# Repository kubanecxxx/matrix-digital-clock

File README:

matrix-digital-clock
====================

Digital clock with homemade LED matrix; STM32 microcontroler; ChibiOS real time operating system

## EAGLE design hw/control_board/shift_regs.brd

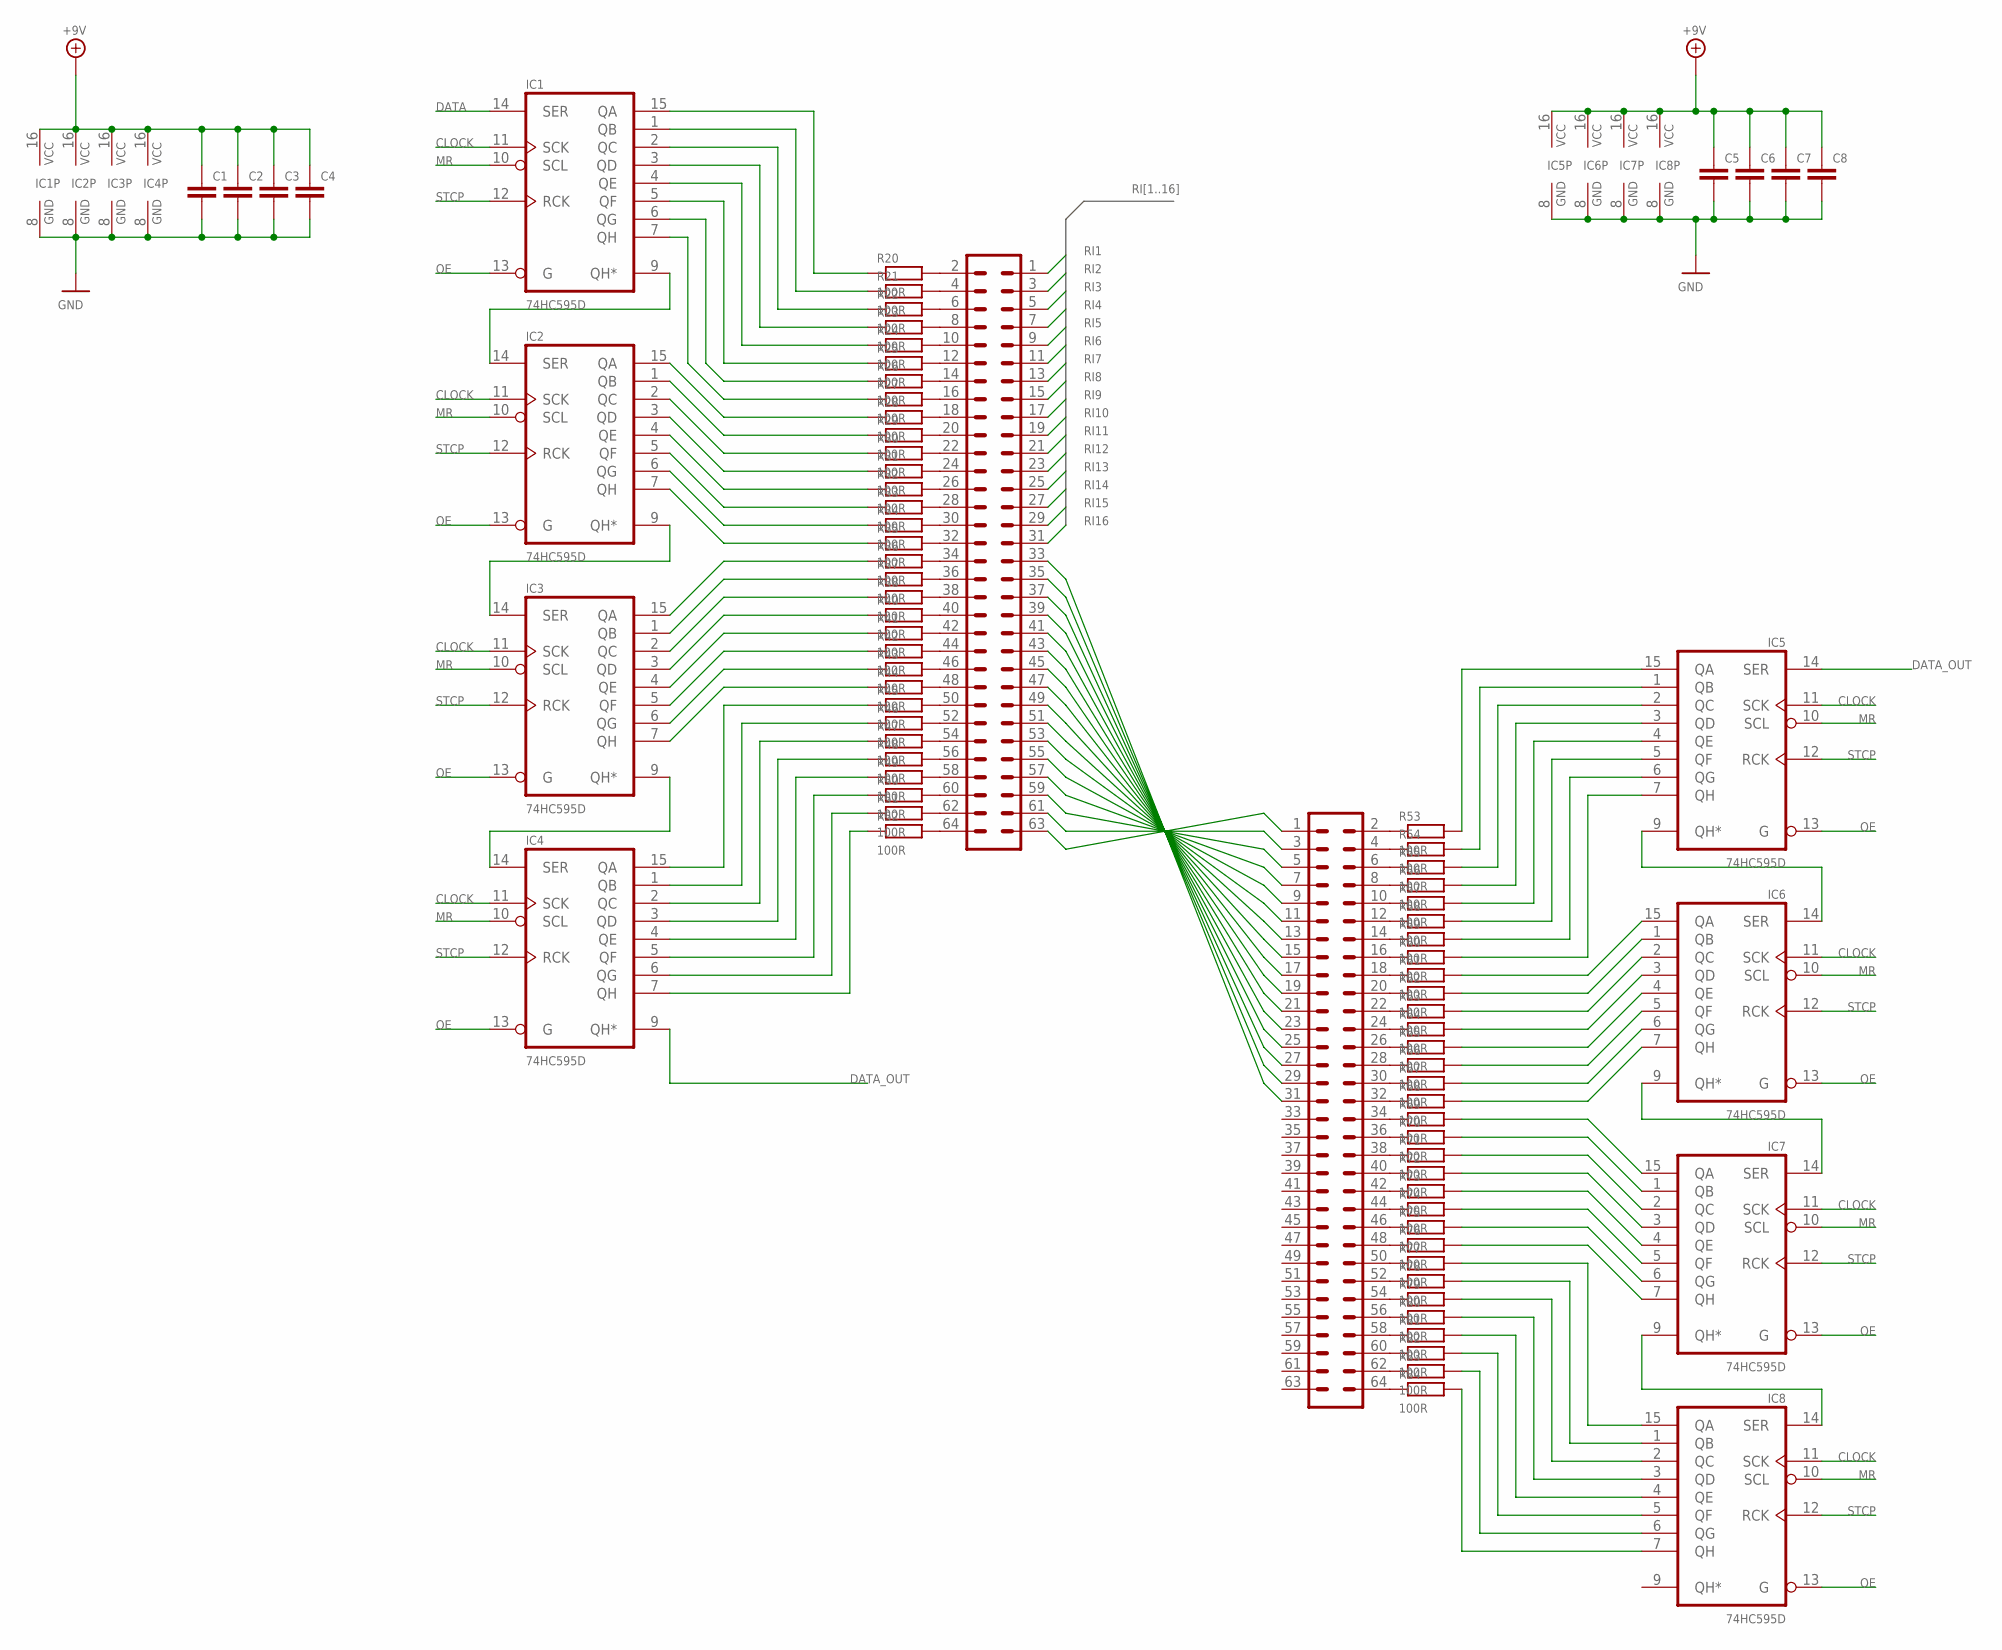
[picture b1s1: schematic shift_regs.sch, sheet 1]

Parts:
C1, C2, C3, C4, C5, C6, C7, C8: C-EUC0805; C0805
IC1, IC2, IC3, IC4, IC5, IC6, IC7, IC8: 74HC595D; SO16
R20, R21, R22, R23, R24, R25, R26, R27, R28, R29, R30, R31, R32, R33, R34, R35, R36, R37, R38, R40, R41, R42, R43, R44, R45, R46, R47, R48, R49, R50, R51, R52, R53, R54, R55, R56, R57, R58, R59, R60, R61, R62, R63, R64, R65, R66, R67, R68, R69, R70, R71, R72, R73, R74, R75, R76, R77, R78, R79, R80, R81, R82, R83, R84: 100R; R0805
SV1, SV2: ML64

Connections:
+9V: C1.1, C2.1, C3.1, C4.1, C5.1, C6.1, C7.1, C8.1, IC1.16 (VCC), IC2.16 (VCC), IC3.16 (VCC), IC4.16 (VCC), IC5.16 (VCC), IC6.16 (VCC), IC7.16 (VCC), IC8.16 (VCC); also elsewhere on the board
CLOCK: IC1.11 (SCK), IC2.11 (SCK), IC3.11 (SCK), IC4.11 (SCK), IC5.11 (SCK), IC6.11 (SCK), IC7.11 (SCK), IC8.11 (SCK); also elsewhere on the board
DATA: IC1.14 (SER); also elsewhere on the board
DATA_OUT: IC4.9 (QH*), IC5.14 (SER)
GND: C1.2, C2.2, C3.2, C4.2, C5.2, C6.2, C7.2, C8.2, IC1.8 (GND), IC2.8 (GND), IC3.8 (GND), IC4.8 (GND), IC5.8 (GND), IC6.8 (GND), IC7.8 (GND), IC8.8 (GND); also elsewhere on the board
MR: IC1.10 (SCL), IC2.10 (SCL), IC3.10 (SCL), IC4.10 (SCL), IC5.10 (SCL), IC6.10 (SCL), IC7.10 (SCL), IC8.10 (SCL); also elsewhere on the board
unnamed: IC1.9 (QH*), IC2.14 (SER)
unnamed: IC2.9 (QH*), IC3.14 (SER)
unnamed: IC3.9 (QH*), IC4.14 (SER)
unnamed: IC1.1 (QB), R21.1
unnamed: IC1.2 (QC), R22.1
unnamed: IC1.3 (QD), R23.1
unnamed: IC1.4 (QE), R24.1
unnamed: IC1.5 (QF), R25.1
unnamed: IC1.6 (QG), R26.1
unnamed: IC1.7 (QH), R27.1
unnamed: IC1.15 (QA), R20.1
unnamed: IC2.1 (QB), R29.1
unnamed: IC2.2 (QC), R30.1
unnamed: IC2.3 (QD), R31.1
unnamed: IC2.4 (QE), R32.1
unnamed: IC2.5 (QF), R33.1
unnamed: IC2.6 (QG), R34.1
unnamed: IC2.7 (QH), R35.1
unnamed: IC2.15 (QA), R28.1
unnamed: IC3.1 (QB), R37.1
unnamed: IC3.2 (QC), R38.1
unnamed: IC3.3 (QD), R40.1
unnamed: IC3.4 (QE), R41.1
unnamed: IC3.5 (QF), R42.1
unnamed: IC3.6 (QG), R43.1
unnamed: IC3.7 (QH), R44.1
unnamed: IC3.15 (QA), R36.1
unnamed: R20.2, SV1.2
unnamed: R21.2, SV1.4
unnamed: R22.2, SV1.6
unnamed: R23.2, SV1.8
unnamed: R24.2, SV1.10
unnamed: R25.2, SV1.12
unnamed: R26.2, SV1.14
unnamed: R27.2, SV1.16
unnamed: IC5.9 (QH*), IC6.14 (SER)
unnamed: IC6.9 (QH*), IC7.14 (SER)
unnamed: IC7.9 (QH*), IC8.14 (SER)
unnamed: IC5.1 (QB), R54.2
unnamed: IC5.2 (QC), R55.2
unnamed: IC5.3 (QD), R56.2
unnamed: IC5.4 (QE), R57.2
unnamed: IC5.5 (QF), R58.2
unnamed: IC5.6 (QG), R59.2
unnamed: IC5.7 (QH), R60.2
unnamed: IC5.15 (QA), R53.2
unnamed: IC6.1 (QB), R62.2
unnamed: IC6.2 (QC), R63.2
unnamed: IC6.3 (QD), R64.2
unnamed: IC6.4 (QE), R65.2
unnamed: IC6.5 (QF), R66.2
unnamed: IC6.6 (QG), R67.2
unnamed: IC6.7 (QH), R68.2
unnamed: IC6.15 (QA), R61.2
unnamed: IC7.1 (QB), R70.2
unnamed: IC7.2 (QC), R71.2
unnamed: IC7.3 (QD), R72.2
unnamed: IC7.4 (QE), R73.2
unnamed: IC7.5 (QF), R74.2
unnamed: IC7.6 (QG), R75.2
unnamed: IC7.7 (QH), R76.2
unnamed: IC7.15 (QA), R69.2
unnamed: IC8.15 (QA), R77.2
unnamed: IC8.1 (QB), R78.2
unnamed: IC8.2 (QC), R79.2
unnamed: IC8.3 (QD), R80.2
unnamed: IC8.4 (QE), R81.2
unnamed: IC8.5 (QF), R82.2
unnamed: IC8.6 (QG), R83.2
unnamed: IC8.7 (QH), R84.2
unnamed: SV1.63, SV2.1
unnamed: SV1.61, SV2.3
unnamed: SV1.59, SV2.5
unnamed: SV1.57, SV2.7
unnamed: SV1.55, SV2.9
unnamed: SV1.53, SV2.11
unnamed: SV1.51, SV2.13
unnamed: SV1.49, SV2.15
unnamed: SV1.47, SV2.17
unnamed: SV1.45, SV2.19
unnamed: SV1.43, SV2.21
unnamed: SV1.41, SV2.23
unnamed: SV1.39, SV2.25
unnamed: SV1.37, SV2.27
unnamed: SV1.35, SV2.29
unnamed: SV1.33, SV2.31
unnamed: R28.2, SV1.18
unnamed: R29.2, SV1.20
unnamed: R30.2, SV1.22
unnamed: R31.2, SV1.24
unnamed: R32.2, SV1.26
unnamed: R33.2, SV1.28
unnamed: R34.2, SV1.30
unnamed: R35.2, SV1.32
unnamed: R36.2, SV1.34
unnamed: R37.2, SV1.36
unnamed: R38.2, SV1.38
unnamed: R40.2, SV1.40
unnamed: R41.2, SV1.42
unnamed: R42.2, SV1.44
unnamed: R43.2, SV1.46
unnamed: R44.2, SV1.48
unnamed: R45.2, SV1.50
unnamed: R46.2, SV1.52
unnamed: R47.2, SV1.54
unnamed: R48.2, SV1.56
unnamed: R49.2, SV1.58
unnamed: R50.2, SV1.60
unnamed: R51.2, SV1.62
unnamed: R52.2, SV1.64
unnamed: R53.1, SV2.2
unnamed: R54.1, SV2.4
unnamed: R55.1, SV2.6
unnamed: IC4.15 (QA), R45.1
unnamed: IC4.1 (QB), R46.1
unnamed: IC4.2 (QC), R47.1
unnamed: IC4.3 (QD), R48.1
unnamed: IC4.4 (QE), R49.1
unnamed: IC4.5 (QF), R50.1
unnamed: IC4.6 (QG), R51.1
unnamed: IC4.7 (QH), R52.1
unnamed: R56.1, SV2.8
unnamed: R57.1, SV2.10
unnamed: R58.1, SV2.12
unnamed: R59.1, SV2.14
unnamed: R60.1, SV2.16
unnamed: R61.1, SV2.18
unnamed: R62.1, SV2.20
unnamed: R63.1, SV2.22
unnamed: R64.1, SV2.24
unnamed: R65.1, SV2.26
unnamed: R66.1, SV2.28
unnamed: R67.1, SV2.30
unnamed: R68.1, SV2.32
unnamed: R69.1, SV2.34
unnamed: R70.1, SV2.36
unnamed: R71.1, SV2.38
unnamed: R72.1, SV2.40
unnamed: R73.1, SV2.42
unnamed: R74.1, SV2.44
unnamed: R75.1, SV2.46
unnamed: R76.1, SV2.48
unnamed: R77.1, SV2.50
unnamed: R78.1, SV2.52
unnamed: R79.1, SV2.54
unnamed: R80.1, SV2.56
unnamed: R81.1, SV2.58
unnamed: R82.1, SV2.60
unnamed: R83.1, SV2.62
unnamed: R84.1, SV2.64
OE: IC1.13 (G), IC2.13 (G), IC3.13 (G), IC4.13 (G), IC5.13 (G), IC6.13 (G), IC7.13 (G), IC8.13 (G); also elsewhere on the board
RI1: SV1.1; also elsewhere on the board
RI2: SV1.3; also elsewhere on the board
RI3: SV1.5; also elsewhere on the board
RI4: SV1.7; also elsewhere on the board
RI5: SV1.9; also elsewhere on the board
RI6: SV1.11; also elsewhere on the board
RI7: SV1.13; also elsewhere on the board
RI8: SV1.15; also elsewhere on the board
RI9: SV1.17; also elsewhere on the board
RI10: SV1.19; also elsewhere on the board
RI11: SV1.21; also elsewhere on the board
RI12: SV1.23; also elsewhere on the board
RI13: SV1.25; also elsewhere on the board
RI14: SV1.27; also elsewhere on the board
RI15: SV1.29; also elsewhere on the board
RI16: SV1.31; also elsewhere on the board
STCP: IC1.12 (RCK), IC2.12 (RCK), IC3.12 (RCK), IC4.12 (RCK), IC5.12 (RCK), IC6.12 (RCK), IC7.12 (RCK), IC8.12 (RCK); also elsewhere on the board

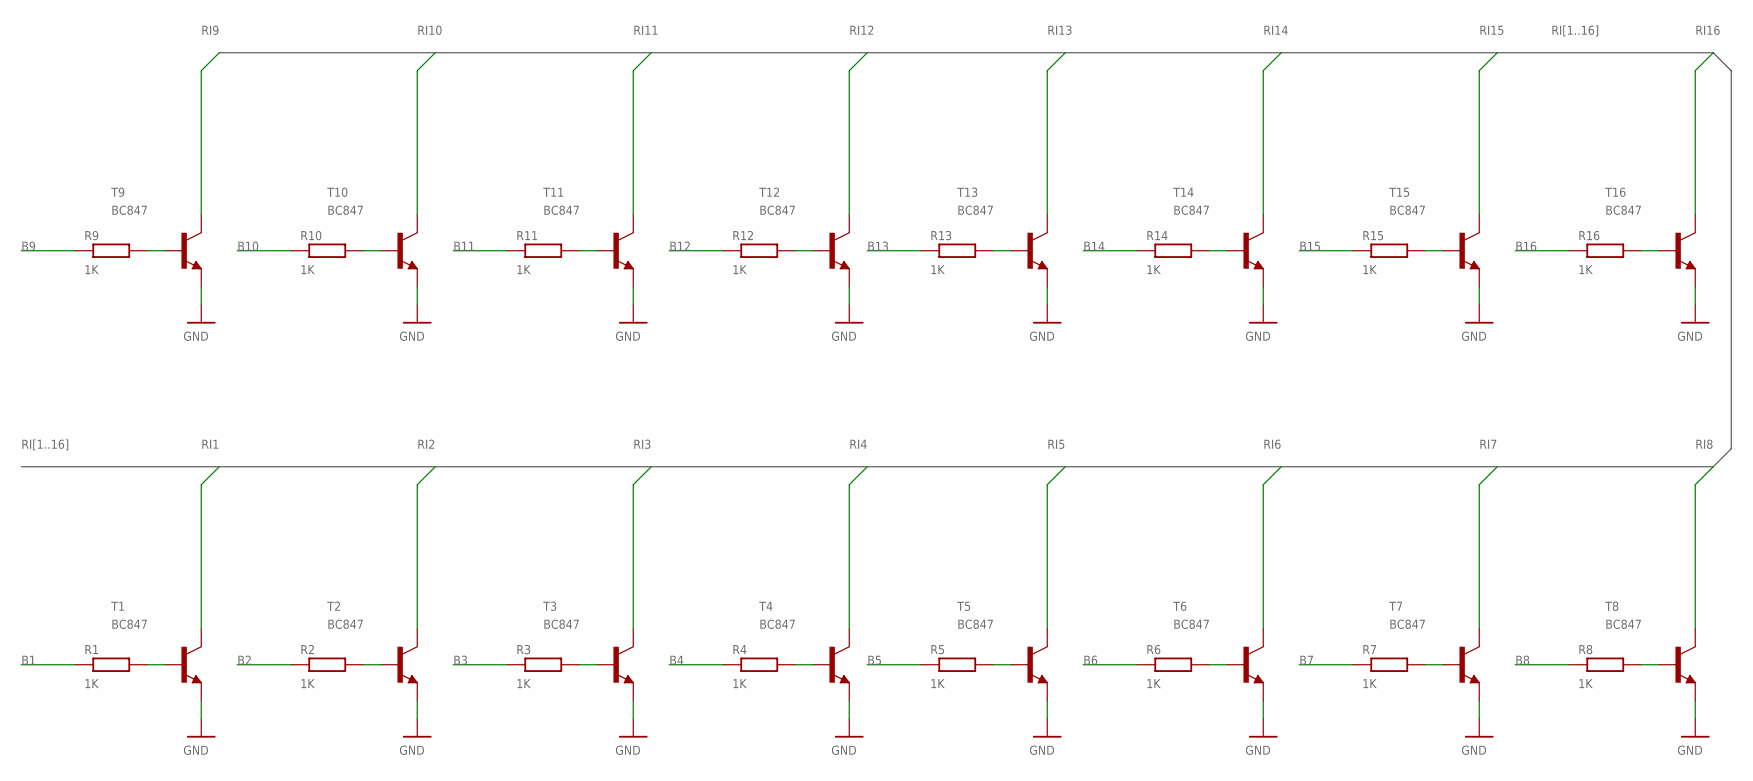
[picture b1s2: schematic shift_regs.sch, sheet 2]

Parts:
R1, R2, R3, R4, R5, R6, R7, R8, R9, R10, R11, R12, R13, R14, R15, R16: 1K; R0805
T1, T2, T3, T4, T5, T6, T7, T8, T9, T10, T11, T12, T13, T14, T15, T16: BC847; SOT23

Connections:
B1: R1.1; also elsewhere on the board
B2: R2.1; also elsewhere on the board
B3: R3.1; also elsewhere on the board
B4: R4.1; also elsewhere on the board
B5: R5.1; also elsewhere on the board
B6: R6.1; also elsewhere on the board
B7: R7.1; also elsewhere on the board
B8: R8.1; also elsewhere on the board
B9: R9.1; also elsewhere on the board
B10: R10.1; also elsewhere on the board
B11: R11.1; also elsewhere on the board
B12: R12.1; also elsewhere on the board
B13: R13.1; also elsewhere on the board
B14: R14.1; also elsewhere on the board
B15: R15.1; also elsewhere on the board
B16: R16.1; also elsewhere on the board
GND: T1.2 (E), T2.2 (E), T3.2 (E), T4.2 (E), T5.2 (E), T6.2 (E), T7.2 (E), T8.2 (E), T9.2 (E), T10.2 (E), T11.2 (E), T12.2 (E), T13.2 (E), T14.2 (E), T15.2 (E), T16.2 (E); also elsewhere on the board
unnamed: R1.2, T1.1 (B)
unnamed: R2.2, T2.1 (B)
unnamed: R3.2, T3.1 (B)
unnamed: R4.2, T4.1 (B)
unnamed: R5.2, T5.1 (B)
unnamed: R6.2, T6.1 (B)
unnamed: R7.2, T7.1 (B)
unnamed: R8.2, T8.1 (B)
unnamed: R9.2, T9.1 (B)
unnamed: R10.2, T10.1 (B)
unnamed: R11.2, T11.1 (B)
unnamed: R12.2, T12.1 (B)
unnamed: R13.2, T13.1 (B)
unnamed: R14.2, T14.1 (B)
unnamed: R15.2, T15.1 (B)
unnamed: R16.2, T16.1 (B)
RI1: T1.3 (C); also elsewhere on the board
RI2: T2.3 (C); also elsewhere on the board
RI3: T3.3 (C); also elsewhere on the board
RI4: T4.3 (C); also elsewhere on the board
RI5: T5.3 (C); also elsewhere on the board
RI6: T6.3 (C); also elsewhere on the board
RI7: T7.3 (C); also elsewhere on the board
RI8: T8.3 (C); also elsewhere on the board
RI9: T9.3 (C); also elsewhere on the board
RI10: T10.3 (C); also elsewhere on the board
RI11: T11.3 (C); also elsewhere on the board
RI12: T12.3 (C); also elsewhere on the board
RI13: T13.3 (C); also elsewhere on the board
RI14: T14.3 (C); also elsewhere on the board
RI15: T15.3 (C); also elsewhere on the board
RI16: T16.3 (C); also elsewhere on the board

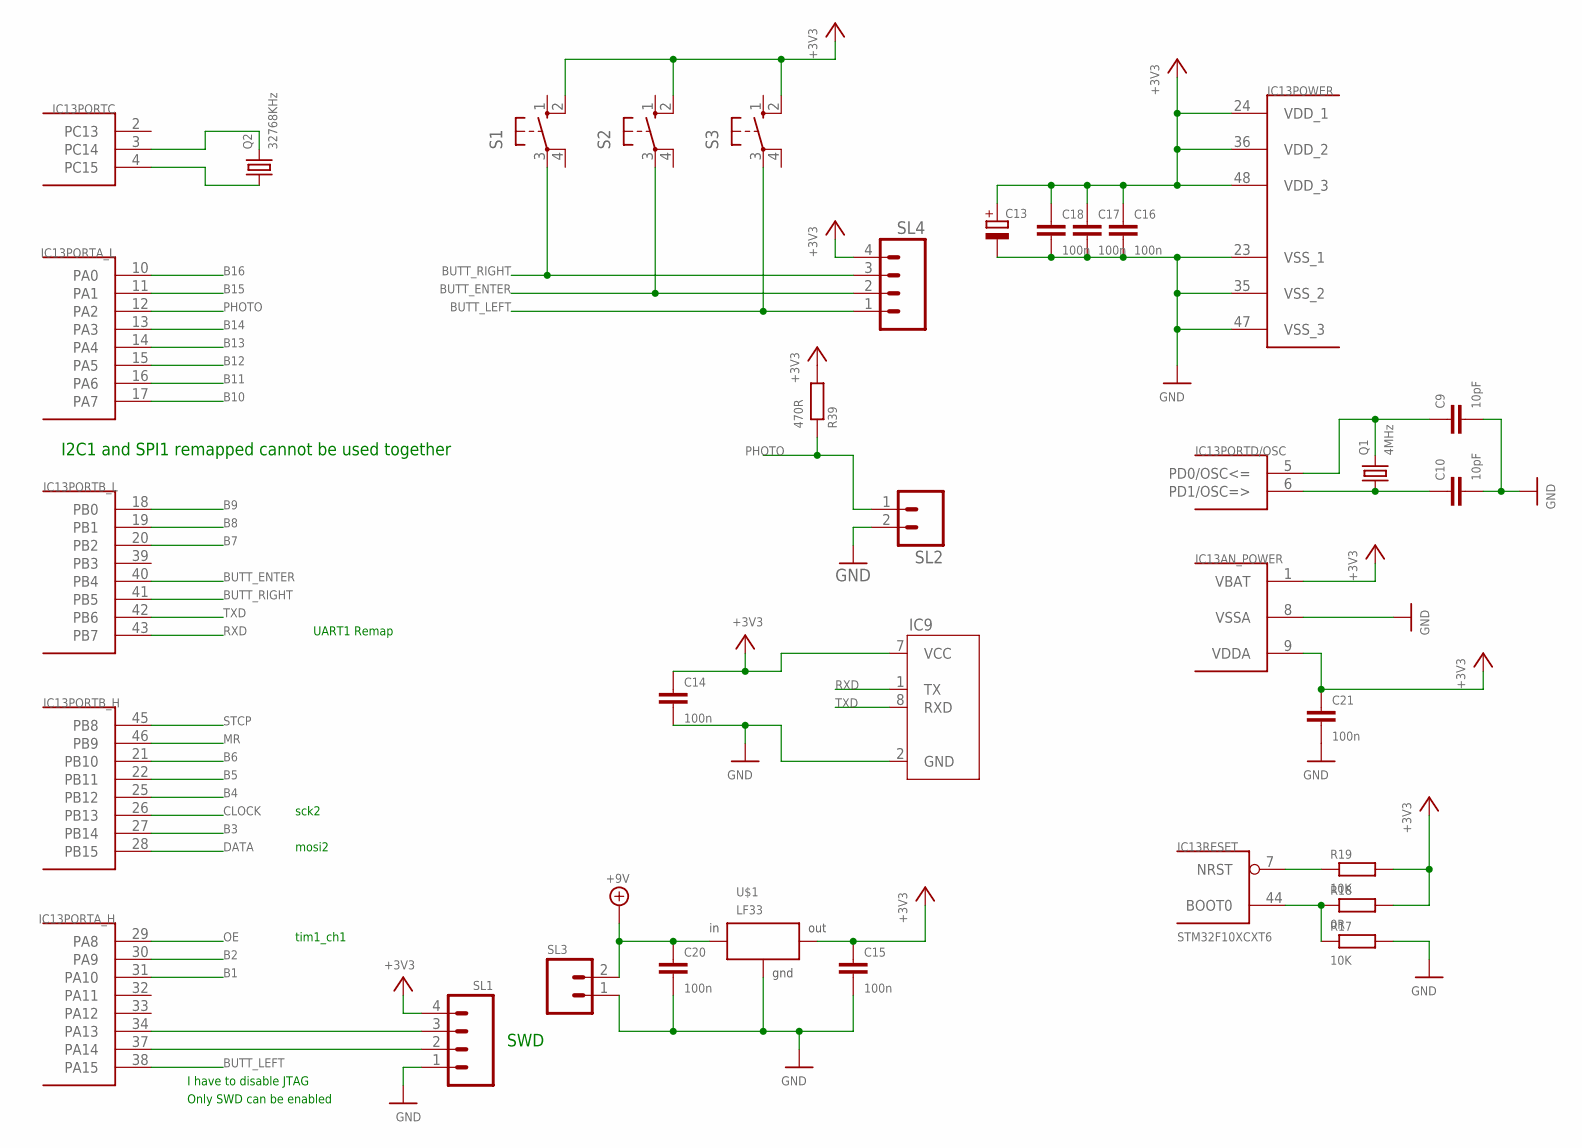
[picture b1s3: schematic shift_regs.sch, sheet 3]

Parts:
C9, C10: 10pF; C0805
C13: CPOL-EUE2.5-6; E2,5-6
C14, C15, C16, C17, C18, C20, C21: 100n; C0805
IC9: ESP8266; NRF24L01
IC13: STM32F10XCXT6; TQFP48
Q1: 4MHz; HC49/S
Q2: 32768KHz; TC26V
R17, R19: 10K; R0805
R18: 0R; R0805
R39: 470R; R0805
S1, S2, S3: 10-XX; B3F-10XX
SL1, SL4: M04; 04P
SL2, SL3: M02; 02P
U$1: LF33; DPACK

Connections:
+3V3: C13.+, C14.1, C15.1, C16.1, C17.1, C18.1, C21.1, IC9.7 (VCC), IC13.1 (VBAT), IC13.9 (VDDA), IC13.24 (VDD_1), IC13.36 (VDD_2), IC13.48 (VDD_3), R18.2, R19.2, R39.2, S1.2 (S1), S2.2 (S1), S3.2 (S1), SL1.4, SL4.4, U$1.3 (OUT)
+9V: C20.1, SL3.2, U$1.1 (IN); also elsewhere on the board
B1: IC13.31 (PA10); also elsewhere on the board
B2: IC13.30 (PA9); also elsewhere on the board
B3: IC13.27 (PB14); also elsewhere on the board
B4: IC13.25 (PB12); also elsewhere on the board
B5: IC13.22 (PB11); also elsewhere on the board
B6: IC13.21 (PB10); also elsewhere on the board
B7: IC13.20 (PB2); also elsewhere on the board
B8: IC13.19 (PB1); also elsewhere on the board
B9: IC13.18 (PB0); also elsewhere on the board
B10: IC13.17 (PA7); also elsewhere on the board
B11: IC13.16 (PA6); also elsewhere on the board
B12: IC13.15 (PA5); also elsewhere on the board
B13: IC13.14 (PA4); also elsewhere on the board
B14: IC13.13 (PA3); also elsewhere on the board
B15: IC13.11 (PA1); also elsewhere on the board
B16: IC13.10 (PA0); also elsewhere on the board
BUTT_ENTER: IC13.40 (PB4), S2.3, SL4.2
BUTT_LEFT: IC13.38 (PA15), S3.3, SL4.1
BUTT_RIGHT: IC13.41 (PB5), S1.3, SL4.3
CLOCK: IC13.26 (PB13); also elsewhere on the board
DATA: IC13.28 (PB15); also elsewhere on the board
GND: C9.2, C10.2, C13.-, C14.2, C15.2, C16.2, C17.2, C18.2, C20.2, C21.2, IC9.2 (GND), IC13.8 (VSSA), IC13.23 (VSS_1), IC13.35 (VSS_2), IC13.47 (VSS_3), R17.2, SL1.1, SL2.2, SL3.1, U$1.2 (GND); also elsewhere on the board
MR: IC13.46 (PB9); also elsewhere on the board
unnamed: IC13.3 (PC14), Q2.2
unnamed: IC13.4 (PC15), Q2.1
unnamed: C9.1, IC13.5 (PD0/OSC<=), Q1.2
unnamed: C10.1, IC13.6 (PD1/OSC=>), Q1.1
unnamed: IC13.44 (BOOT0), R17.1, R18.1
NRST: IC13.7 (NRST), R19.1
OE: IC13.29 (PA8); also elsewhere on the board
PHOTO: IC13.12 (PA2), R39.1, SL2.1
RXD: IC9.1 (TX), IC13.43 (PB7)
STCP: IC13.45 (PB8); also elsewhere on the board
SWDCLK: IC13.37 (PA14), SL1.2
SWDIO: IC13.34 (PA13), SL1.3
TXD: IC9.8 (RXD), IC13.42 (PB6)

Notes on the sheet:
SWD
I have to disable JTAG
I2C1 and SPI1 remapped cannot be used together
Only SWD can be enabled
sck2
mosi2
tim1_ch1
UART1 Remap

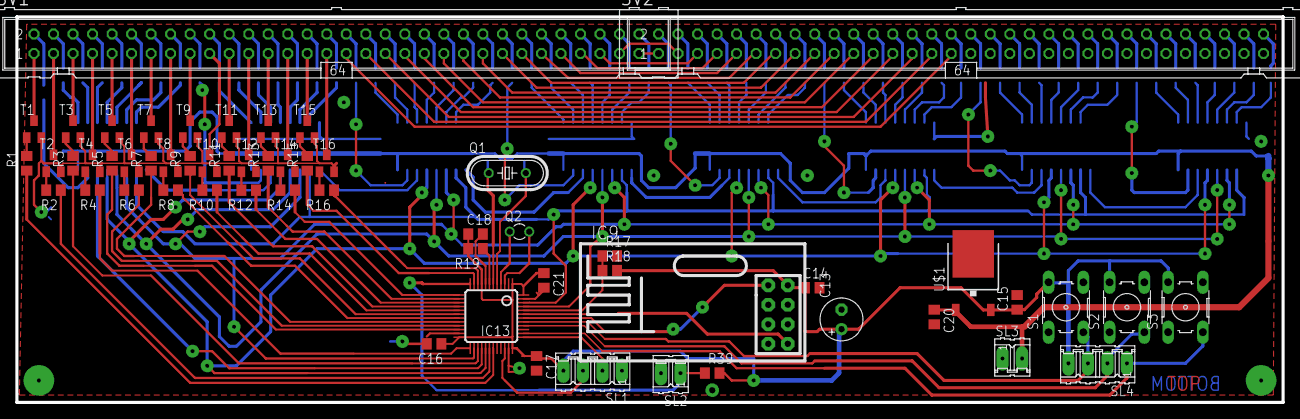
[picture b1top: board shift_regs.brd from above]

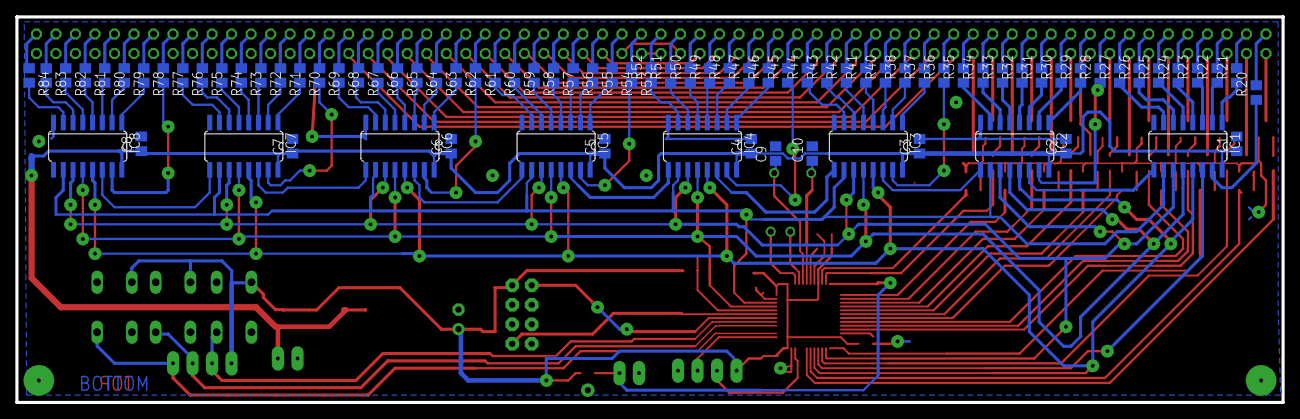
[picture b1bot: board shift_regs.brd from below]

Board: 2 copper layers, 164.8 x 50.2 mm, 140 parts (82 on the bottom side), 221 nets.

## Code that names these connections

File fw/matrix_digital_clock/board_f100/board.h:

/*
    ChibiOS/RT - Copyright (C) 2006,2007,2008,2009,2010,
                 2011,2012 Giovanni Di Sirio.

    This file is part of ChibiOS/RT.

    ChibiOS/RT is free software; you can redistribute it and/or modify
    it under the terms of the GNU General Public License as published by
    the Free Software Foundation; either version 3 of the License, or
    (at your option) any later version.

    ChibiOS/RT is distributed in the hope that it will be useful,
    but WITHOUT ANY WARRANTY; without even the implied warranty of
    MERCHANTABILITY or FITNESS FOR A PARTICULAR PURPOSE.  See the
    GNU General Public License for more details.

    You should have received a copy of the GNU General Public License
    along with this program.  If not, see <http://www.gnu.org/licenses/>.
*/

#ifndef _BOARD_H_
#define _BOARD_H_

/*
 * Setup for STMicroelectronics STM32VL-Discovery board.
 */

/*
 * Board identifier.
 */
//#define BOARD_ST_STM32VL_DISCOVERY
#define BOARD_NAME              "ST Routerboard"

/*
 * Board frequencies.
 */
#define STM32_LSECLK            32768
#define STM32_HSECLK            4000000

/*
 * MCU type, supported types are defined in ./os/hal/platforms/hal_lld.h.
 */
#define STM32F10X_MD_VL

/*
 * IO pins assignments.
 */
#define GPIOA_BUTTON            0
#define GPIOA_SPI1NSS           4

#define GPIOB_SPI2NSS           12

#define GPIOC_LED4              8
#define GPIOC_LED3              9

/*
 * I/O ports initial setup, this configuration is established soon after reset
 * in the initialization code.
 *
 * The digits have the following meaning:
 *   0 - Analog input.
 *   1 - Push Pull output 10MHz.
 *   2 - Push Pull output 2MHz.
 *   3 - Push Pull output 50MHz.
 *   4 - Digital input.
 *   5 - Open Drain output 10MHz.
 *   6 - Open Drain output 2MHz.
 *   7 - Open Drain output 50MHz.
 *   8 - Digital input with PullUp or PullDown resistor depending on ODR.
 *   9 - Alternate Push Pull output 10MHz.
 *   A - Alternate Push Pull output 2MHz.
 *   B - Alternate Push Pull output 50MHz.
 *   C - Reserved.
 *   D - Alternate Open Drain output 10MHz.
 *   E - Alternate Open Drain output 2MHz.
 *   F - Alternate Open Drain output 50MHz.
 * Please refer to the STM32 Reference Manual for details.
 */

/*
 * Port A setup.
 * Everything input with pull-up except:
 * PA0  - Normal input      (BUTTON).
 * PA2  - Alternate output  (USART2 TX).
 * PA3  - Normal input      (USART2 RX).
 * PA4  - Push pull output  (SPI1 NSS), initially high state.
 * PA5  - Alternate output  (SPI1 SCK).
 * PA6  - Normal input      (SPI1 MISO).
 * PA7  - Alternate output  (SPI1 MOSI).
 * PA9  - Alternate output  (USART1 TX).
 * PA10 - Normal input      (USART1 RX).
 */
#define VAL_GPIOACRL            0xB4B33333      /*  PA7...PA0 */
#define VAL_GPIOACRH            0x888884B8      /* PA15...PA8 */
#define VAL_GPIOAODR            0xFFFFFFFF

/*
 * Port B setup.
 * Everything input with pull-up except:
 * PB12 - Push pull output  (SPI2 NSS), initially high state.
 * PB13 - Alternate output  (SPI2 SCK).
 * PB14 - Normal input      (SPI2 MISO).
 * PB15 - Alternate output  (SPI2 MOSI).
 */
#define VAL_GPIOBCRL            0x88888888      /*  PB7...PB0 */
#define VAL_GPIOBCRH            0xB4B38888      /* PB15...PB8 */
#define VAL_GPIOBODR            0xFFFFFFFF

/*
 * Port C setup.
 * Everything input with pull-up except:
 * PC8  - Push-pull output (LED4), initially low state.
 * PC9  - Push-pull output (LED3), initially low state.
 */
#define VAL_GPIOCCRL            0x88888888      /*  PC7...PC0 */
#define VAL_GPIOCCRH            0x88888833      /* PC15...PC8 */
#define VAL_GPIOCODR            0xFFFFFCFF

/*
 * Port D setup.
 * Everything input with pull-up except:
 * PD0  - Normal input (XTAL).
 * PD1  - Normal input (XTAL).
 */
#define VAL_GPIODCRL            0x88888844      /*  PD7...PD0 */
#define VAL_GPIODCRH            0x88888888      /* PD15...PD8 */
#define VAL_GPIODODR            0xFFFFFFFF

/*
 * Port E setup.
 * Everything input with pull-up except:
 */
#define VAL_GPIOECRL            0x88888888      /*  PE7...PE0 */
#define VAL_GPIOECRH            0x88888888      /* PE15...PE8 */
#define VAL_GPIOEODR            0xFFFFFFFF

#if !defined(_FROM_ASM_)
#ifdef __cplusplus
extern "C" {
#endif
  void boardInit(void);
#ifdef __cplusplus
}
#endif
#endif /* _FROM_ASM_ */

#endif /* _BOARD_H_ */

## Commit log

2014-09-02 added first hardware - digital matrix PCB start
2014-09-09 finished LED matrix PCB and sent to the chinese production
2014-09-25 shift register hardware layout finished
2014-10-09 finished hardware prototype on my table
    finished led matrix driving with different pixel brightness possibility
    finished part of matrix abstraction layer - text printing and some
    animations - fade, slide
    todo: wireless rf24; modes abstraction and switching, pwm OE
2014-10-16 fixed animations for different font sizes added suppport for different fonts added new led 'font'
    added wireless module rf24 communication with openwrt router
    rtc updating via wirelesss
2014-10-16 slight change in library - added ifeq for each module in library - so added configuration to makefile
2014-10-16 deleted common library because project has become submodule of homeautomation project
2015-02-03 started with dcf feature
2015-06-24 finished
2015-06-30 hardware corrections
2015-07-05 when hours is below 10 -> zero is hidden
2015-12-15 added advanced version with menu and it uses cmake build system
2015-12-15 added smaller version of hardware - two segments only cmake fixes
2015-12-16 menu working
2015-12-16 refactoring - screen class divided into derived classes
2015-12-16 combobox refactored
2015-12-16 number edit refactoring
2015-12-16 refactoring time
2015-12-17 refactoring tested - now it could be squashed
2015-12-17 changed time screen
2015-12-17 added full clocks features
2015-12-18 added flash writing support
2016-01-03 cmake fix
2016-01-07 added wifi support time synchronization from the internet
2016-01-08 added simple ntp time synchronization from internet
2016-05-09 daylight saving time
2017-02-20 great renaming and tidying up
2017-02-20 upgraded hw for version 2 - added header for buttons
2017-02-21 old version removed and put into separate branch called version1
2017-02-21 Selected the right ChibiOS commit
2017-03-29 added control buttons to the control PCB
